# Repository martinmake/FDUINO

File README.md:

# slate_vixen
## DISCLAIMER
This project depends on: https://github.com/martinmake/AVR_libs.git
## HOW TO COMPILE
1. configure LDIR in Makefile
2. make
3. enjoy

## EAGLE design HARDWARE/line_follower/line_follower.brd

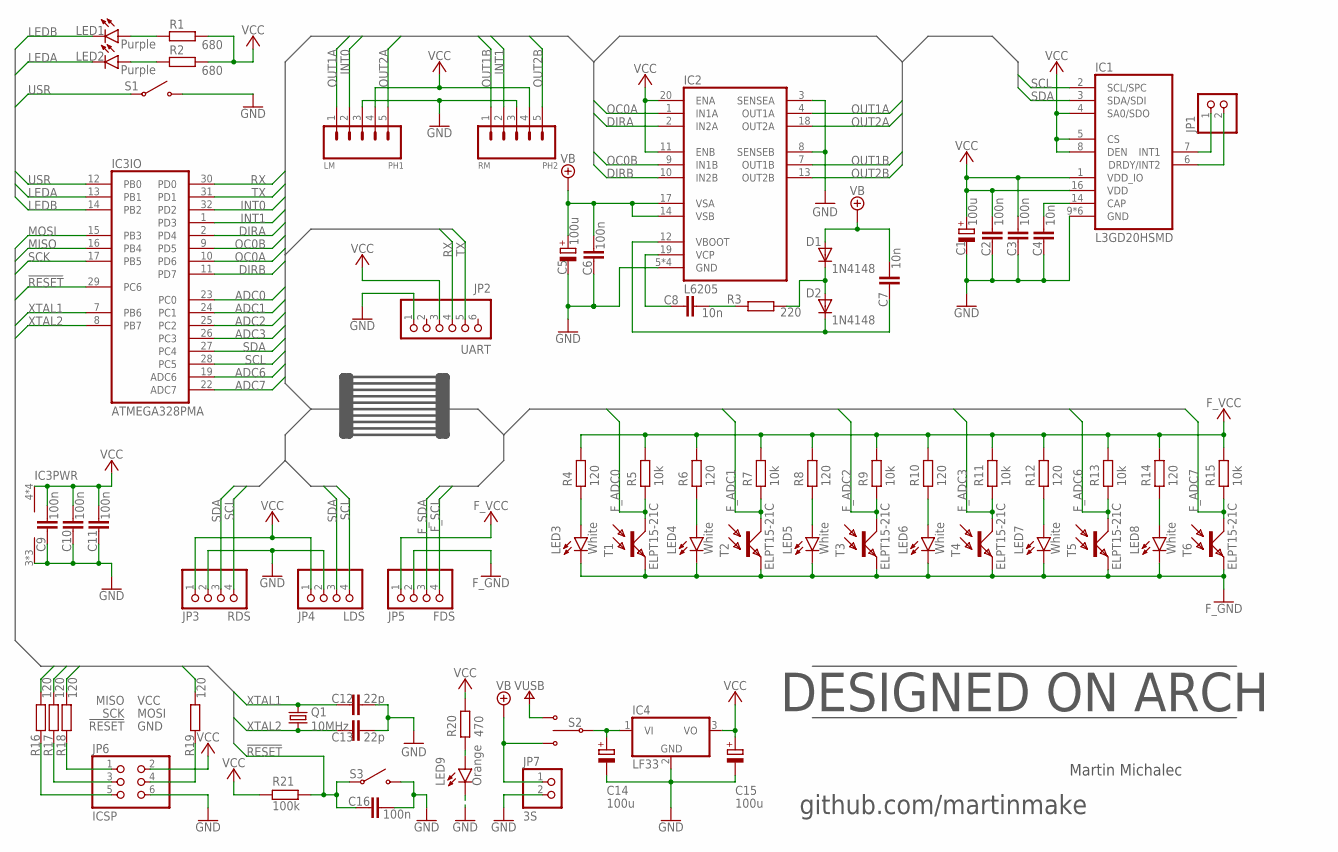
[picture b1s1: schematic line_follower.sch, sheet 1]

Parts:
C1, C5, C14, C15: 100u; UD-6,3X5,8_NICHICON
C2, C3, C6, C9, C10, C11, C16: 100n; C1206
C4, C7, C8: 10n; C1206
C12, C13: 22p; C1206
D1, D2: 1N4148; 1206
IC1: L3GD20HSMD; LGA-16
IC2: L6205; SO20
IC3: ATMEGA328PMA; TQFP32
IC4: LF33; TO220H
JP1: PINHD-1X2; 1X02
JP2: UART; 1X06
JP3: RDS; 1X04/90
JP4: LDS; 1X04/90
JP5: FDS; 1X04/90
JP6: ICSP; 2X03
JP7: 3S; 1X02
LED1, LED2: Purple; SML1206
LED3, LED4, LED5, LED6, LED7, LED8: White; SML1206
LED9: Orange; SML1206
PH1: LM; JST-5-PTH-VERT
PH2: RM; JST-5-PTH-VERT
Q1: 10MHz; CSM-7X-DU
R1, R2: 680; R1206
R3: 220; R1206
R4, R6, R8, R10, R12, R14, R16, R17, R18, R19: 120; R1206
R5, R7, R9, R11, R13, R15: 10k; R1206
R20: 470; R1206
R21: 100k; R1206
S1, S3: BUTTON
S2: DUALSWITCH
T1, T2, T3, T4, T5, T6: ELPT15-21C; 1206

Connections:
!RESET: C16.1, IC3.29 (PC6), R16.2, R21.2, S3.A@1 (1), S3.A@2 (1)
ADC0: IC3.23 (PC0); also elsewhere on the board
ADC1: IC3.24 (PC1); also elsewhere on the board
ADC2: IC3.25 (PC2); also elsewhere on the board
ADC3: IC3.26 (PC3); also elsewhere on the board
ADC6: IC3.19 (ADC6); also elsewhere on the board
ADC7: IC3.22 (ADC7); also elsewhere on the board
DIRA: IC2.2 (IN2A), IC3.2 (PD4)
DIRB: IC2.10 (IN2B), IC3.11 (PD7)
F_ADC0: R5.2, T1.1 (C); also elsewhere on the board
F_ADC1: R7.2, T2.1 (C); also elsewhere on the board
F_ADC2: R9.2, T3.1 (C); also elsewhere on the board
F_ADC3: R11.2, T4.1 (C); also elsewhere on the board
F_ADC6: R13.2, T5.1 (C); also elsewhere on the board
F_ADC7: R15.2, T6.1 (C); also elsewhere on the board
F_GND: JP5.2, LED3.C, LED4.C, LED5.C, LED6.C, LED7.C, LED8.C, T1.2 (E), T2.2 (E), T3.2 (E), T4.2 (E), T5.2 (E), T6.2 (E); also elsewhere on the board
F_SCL: JP5.4; also elsewhere on the board
F_SDA: JP5.3; also elsewhere on the board
F_VCC: JP5.1, R4.1, R5.1, R6.1, R7.1, R8.1, R9.1, R10.1, R11.1, R12.1, R13.1, R14.1, R15.1; also elsewhere on the board
GND: C1.-, C2.2, C3.2, C4.2, C5.-, C6.2, C9.2, C10.2, C11.2, C12.1, C13.1, C14.-, C15.-, C16.2, IC1.9 (GND), IC1.10 (GND), IC1.11 (GND), IC1.12 (GND), IC1.13 (GND), IC1.15 (GND), IC2.3 (SENSEA), IC2.5 (GND), IC2.6 (GND), IC2.8 (SENSEB), IC2.15 (GND), IC2.16 (GND), IC3.3 (GND), IC3.5 (GND), IC3.21 (GND), IC4.2 (GND), JP2.1, JP3.2, JP4.2, JP6.6, JP7.2, LED9.C, PH1.3, PH2.3, S1.B@1 (2), S1.B@2 (2), S3.B@1 (2), S3.B@2 (2); also elsewhere on the board
INT0: IC3.32 (PD2), PH1.2
INT1: IC3.1 (PD3), PH2.2
LEDA: IC3.13 (PB1), LED2.C
LEDB: IC3.14 (PB2), LED1.C
MISO: IC3.16 (PB4), R18.2
MOSI: IC3.15 (PB3), R19.2
unnamed: LED5.A, R8.2
unnamed: C7.1, D2.2 (C), IC2.12 (VBOOT)
unnamed: D1.2 (C), D2.1 (A), R3.2
unnamed: C8.2, R3.1
unnamed: LED1.A, R1.1
unnamed: C4.1, IC1.14 (CAP)
unnamed: C8.1, IC2.19 (VCP)
unnamed: IC1.7 (INT1), JP1.1
unnamed: IC1.6 (DRDY/INT2), JP1.2
unnamed: C14.+, IC4.1 (VI), S2.COM
unnamed: LED6.A, R10.2
unnamed: LED2.A, R2.1
unnamed: LED8.A, R14.2
unnamed: LED7.A, R12.2
unnamed: JP6.1, R18.1
unnamed: LED9.A, R20.2
unnamed: LED4.A, R6.2
unnamed: LED3.A, R4.2
unnamed: JP6.3, R17.1
unnamed: JP6.5, R16.1
unnamed: JP6.4, R19.1
OC0A: IC2.1 (IN1A), IC3.10 (PD6)
OC0B: IC2.9 (IN1B), IC3.9 (PD5)
OUT1A: IC2.4 (OUT1A), PH1.1
OUT1B: IC2.7 (OUT1B), PH2.1
OUT2A: IC2.18 (OUT2A), PH1.5
OUT2B: IC2.13 (OUT2B), PH2.5
RX: IC3.30 (PD0), JP2.4
SCK: IC3.17 (PB5), R17.2
SCL: IC1.2 (SCL/SPC), IC3.28 (PC5), JP3.4, JP4.4; also elsewhere on the board
SDA: IC1.3 (SDA/SDI), IC3.27 (PC4), JP3.3, JP4.3; also elsewhere on the board
TX: IC3.31 (PD1), JP2.5
USR: IC3.12 (PB0), S1.A@1 (1), S1.A@2 (1)
VB: C5.+, C6.1, C7.2, D1.1 (A), IC2.14 (VSB), IC2.17 (VSA), JP7.1, S2.A
VCC: C1.+, C2.1, C3.1, C9.1, C10.1, C11.1, C15.+, IC1.1 (VDD_IO), IC1.4 (SA0/SDO), IC1.5 (CS), IC1.8 (DEN), IC1.16 (VDD), IC2.11 (ENB), IC2.20 (ENA), IC3.4 (VCC), IC3.6 (VCC), IC3.18 (VCC), IC3.20 (VCC), IC4.3 (VO), JP2.3, JP3.1, JP4.1, JP6.2, PH1.4, PH2.4, R1.2, R2.2, R20.1, R21.1; also elsewhere on the board
VUSB: S2.B; also elsewhere on the board
XTAL1: C12.2, IC3.7 (PB6), Q1.2
XTAL2: C13.2, IC3.8 (PB7), Q1.1

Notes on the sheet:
DESIGNED ON ARCH
Martin Michalec
github.com/martinmake

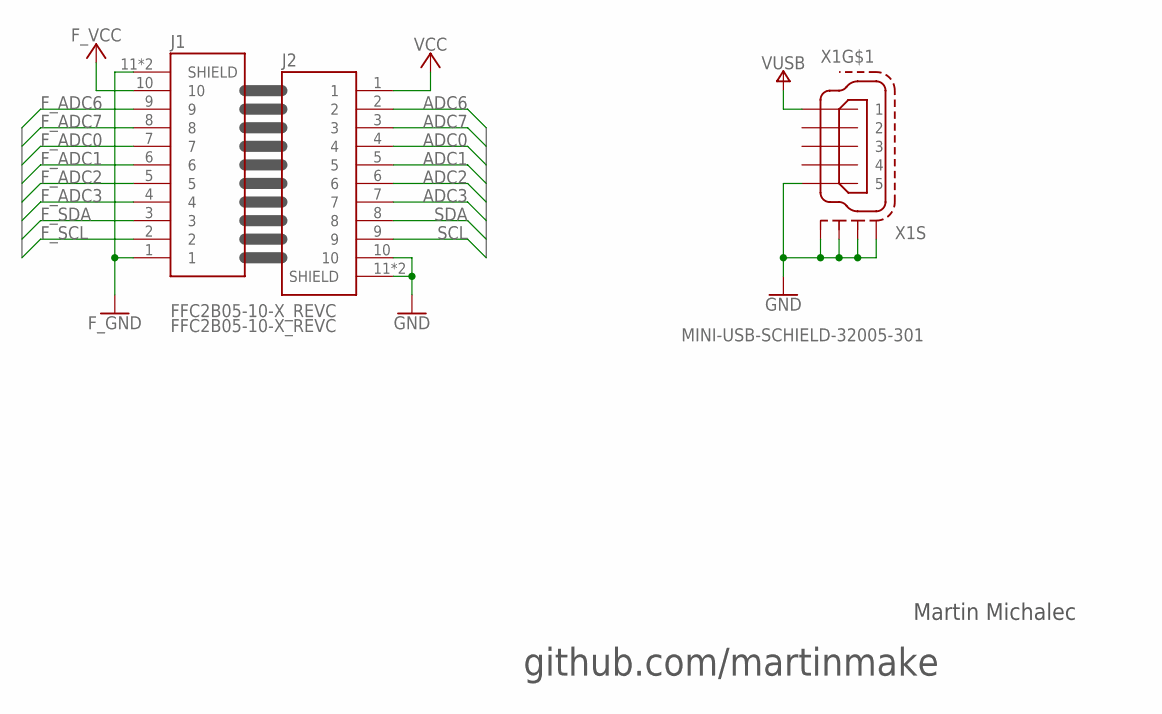
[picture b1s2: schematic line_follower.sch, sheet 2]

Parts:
J1, J2: FFC2B05-10-X_REVC; GCT_FFC2B05-10-X_REVC
X1: MINI-USB-SCHIELD-32005-301; 32005-301

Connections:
ADC0: J2.4; also elsewhere on the board
ADC1: J2.5; also elsewhere on the board
ADC2: J2.6; also elsewhere on the board
ADC3: J2.7; also elsewhere on the board
ADC6: J2.2; also elsewhere on the board
ADC7: J2.3; also elsewhere on the board
F_ADC0: J1.7; also elsewhere on the board
F_ADC1: J1.6; also elsewhere on the board
F_ADC2: J1.5; also elsewhere on the board
F_ADC3: J1.4; also elsewhere on the board
F_ADC6: J1.9; also elsewhere on the board
F_ADC7: J1.8; also elsewhere on the board
F_GND: J1.1, J1.11 (SHIELD), J1.12 (SHIELD); also elsewhere on the board
F_SCL: J1.2; also elsewhere on the board
F_SDA: J1.3; also elsewhere on the board
F_VCC: J1.10; also elsewhere on the board
GND: J2.10, J2.11 (SHIELD), J2.12 (SHIELD), X1.5, X1.M1 (S1), X1.M2 (S2), X1.M3 (S3), X1.M4 (S4); also elsewhere on the board
SCL: J2.9; also elsewhere on the board
SDA: J2.8; also elsewhere on the board
VCC: J2.1; also elsewhere on the board
VUSB: X1.1; also elsewhere on the board

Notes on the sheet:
Martin Michalec
github.com/martinmake

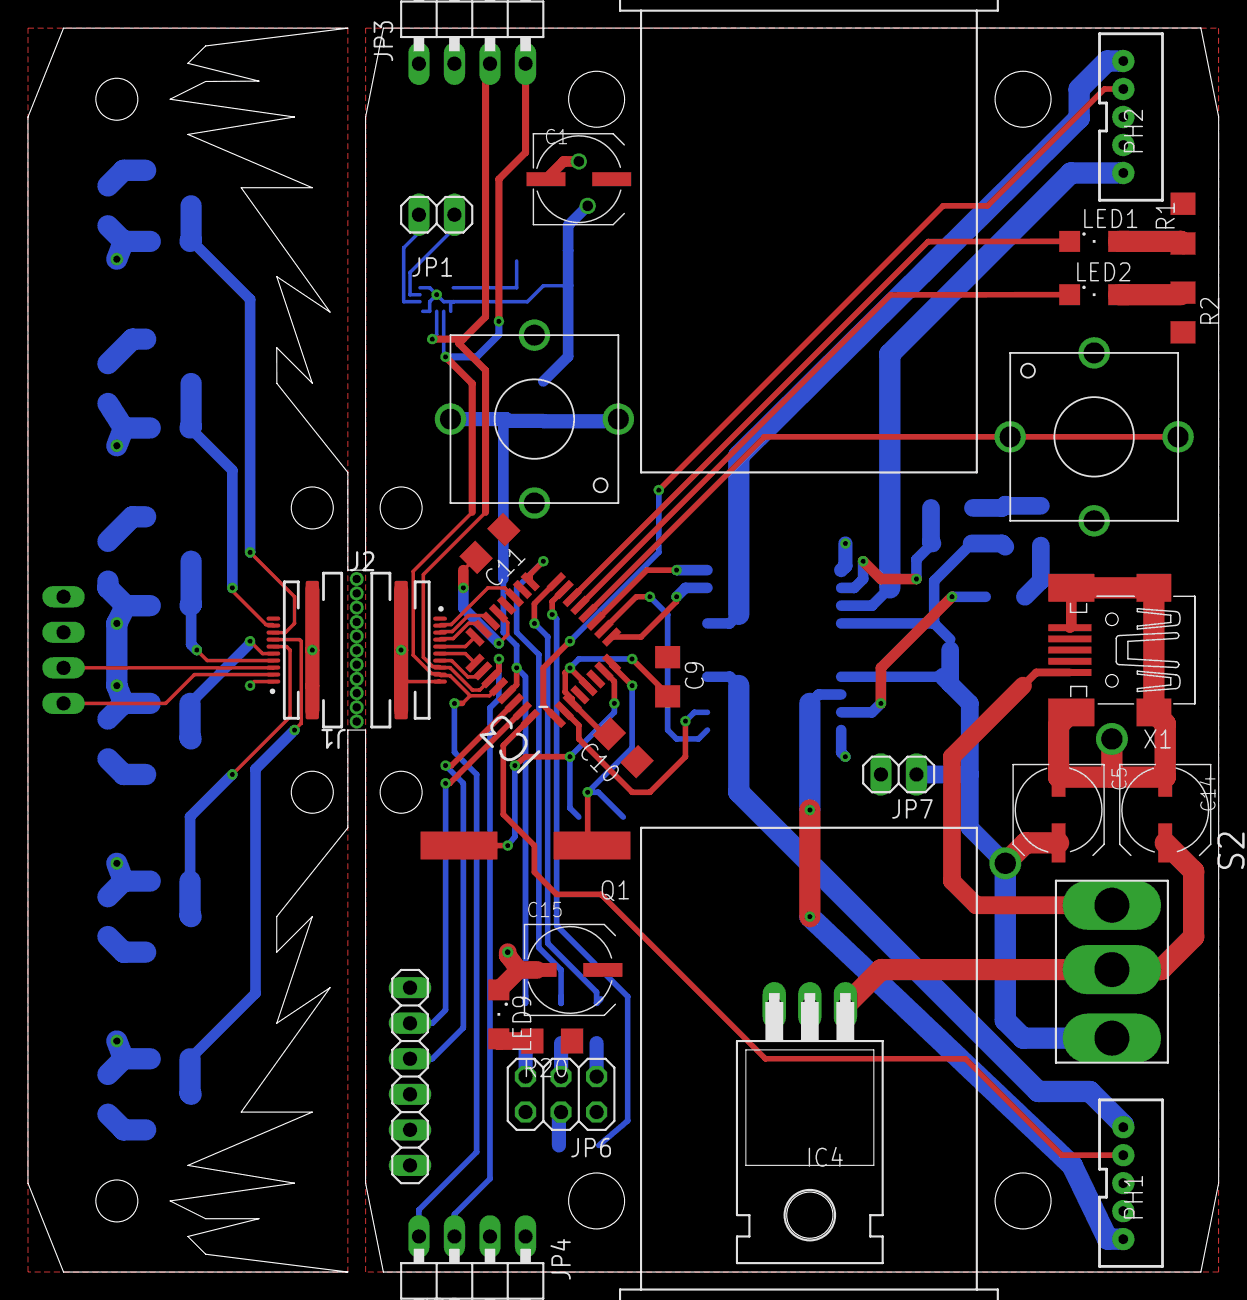
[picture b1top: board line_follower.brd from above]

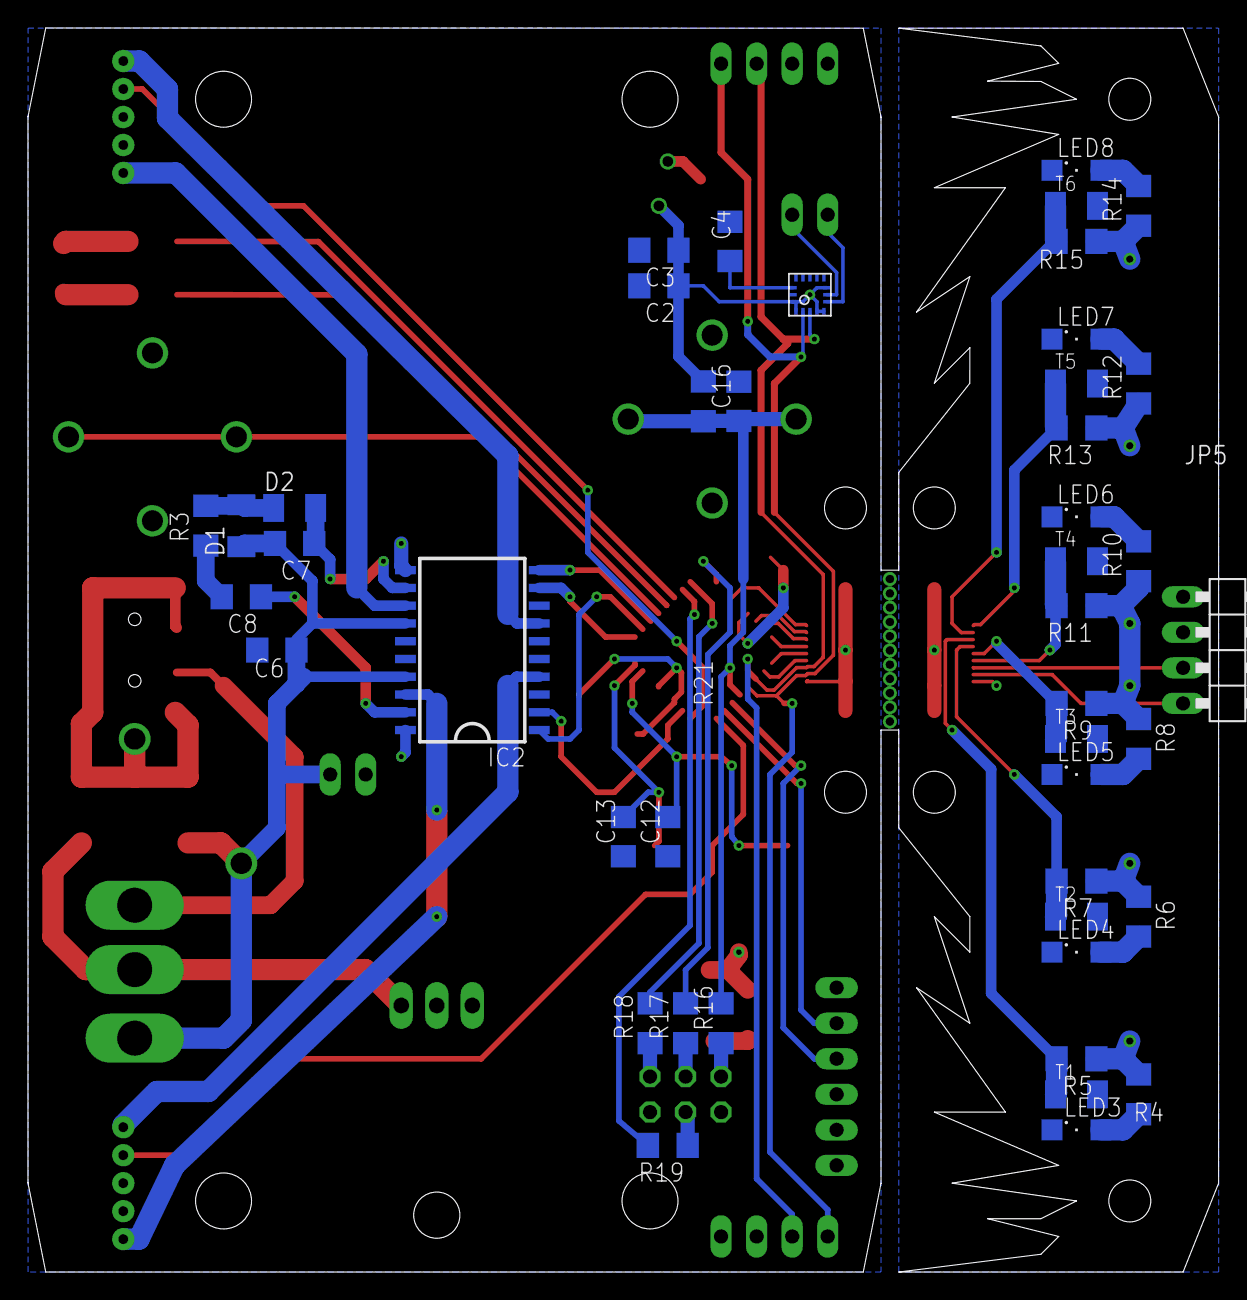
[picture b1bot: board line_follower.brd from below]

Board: 2 copper layers, 85.1 x 88.9 mm, 74 parts (44 on the bottom side), 64 nets.

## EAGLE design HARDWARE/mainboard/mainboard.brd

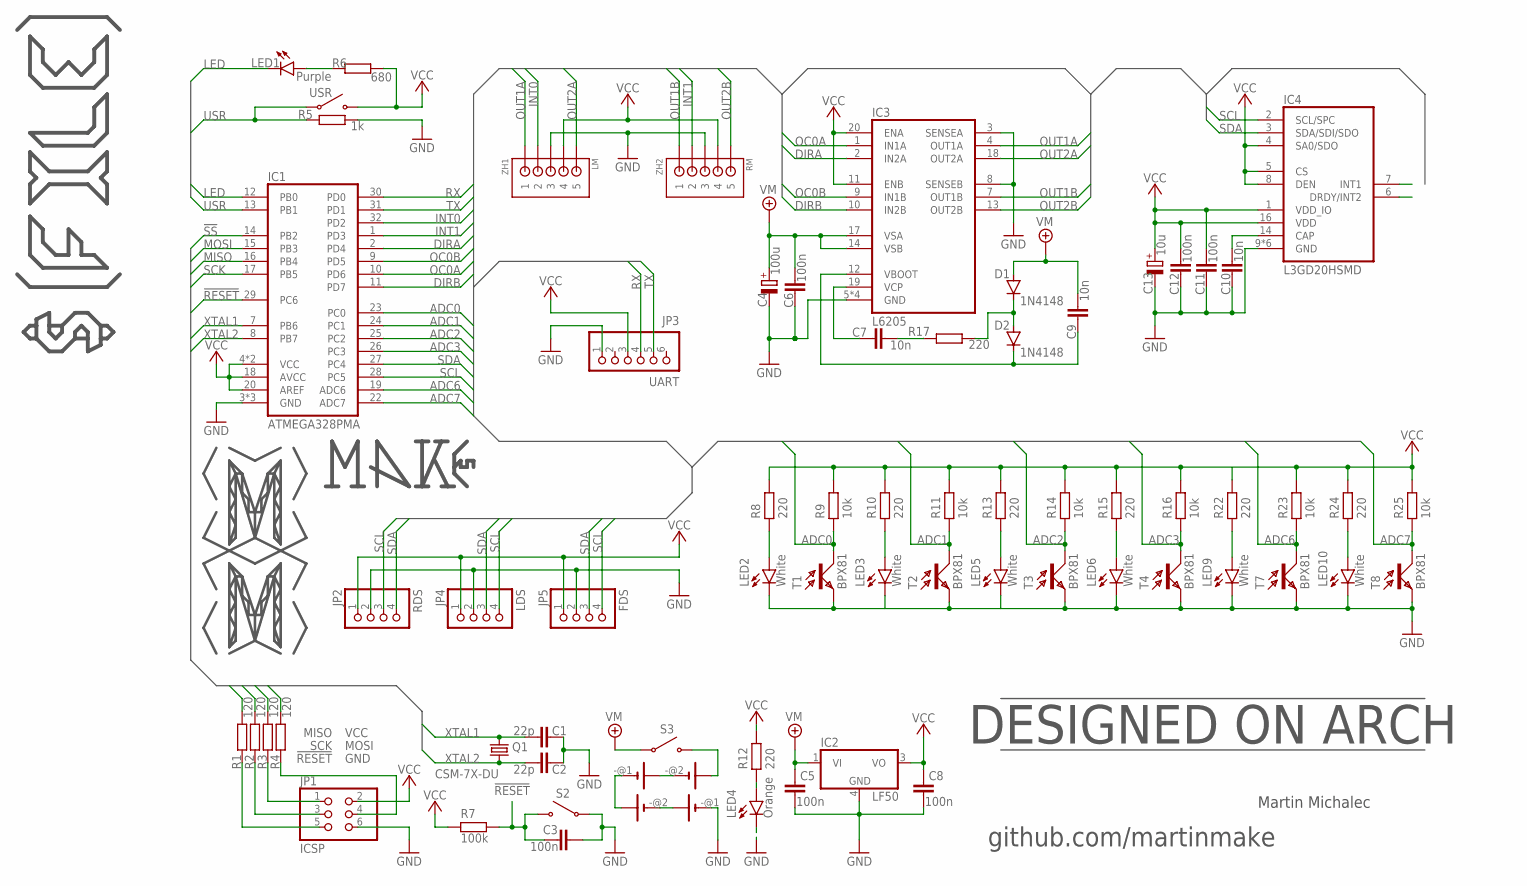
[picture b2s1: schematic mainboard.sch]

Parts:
BAT1, BAT2: BATSERIES; BAT2X18650SERIES
C1, C2: 22p; C1206
C3, C5, C6, C8, C11, C12: 100n; C1206
C4: 100u; SMC_D
C7, C9, C10: 10n; C1206
C13: 10u; SMC_D
D1, D2: 1N4148; DO35-7
IC1: ATMEGA328PMA; TQFP32
IC2: LF50; SOT223
IC3: L6205; SO20
IC4: L3GD20HSMD; LGA-16
JP1: ICSP; 2X03
JP2: RDS; 1X04/90
JP3: UART; 1X06/90
JP4: LDS; 1X04/90
JP5: FDS; 1X04/90
LED1: Purple; SML1206
LED2, LED3, LED5, LED6, LED9, LED10: White; SML1206
LED4: Orange; SML1206
Q1: CSM-7X-DU
R1, R2, R3, R4: 120; R1206
R5: 1k; R1206
R6: 680; R1206
R7: 100k; R1206
R8, R10, R12, R13, R15, R17, R22, R24: 220; R1206
R9, R11, R14, R16, R23, R25: 10k; R1206
S2, S3: SWITCHTHT; SWITCH
T1, T2, T3, T4, T7, T8: BPX81
USR: SWITCHTHT; SWITCH
ZH1: LM; B5B-ZR
ZH2: RM; B5B-ZR

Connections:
!RESET: C3.1, IC1.29 (PC6), R1.2, R7.2, S2.P$2 (2)
!SS: IC1.14 (PB2)
ADC0: IC1.23 (PC0), R9.2, T1.C
ADC1: IC1.24 (PC1), R11.2, T2.C
ADC2: IC1.25 (PC2), R14.2, T3.C
ADC3: IC1.26 (PC3), R16.2, T4.C
ADC6: IC1.19 (ADC6), R23.2, T7.C
ADC7: IC1.22 (ADC7), R25.2, T8.C
DIRA: IC1.2 (PD4), IC3.2 (IN2A)
DIRB: IC1.11 (PD7), IC3.10 (IN2B)
GND: BAT2.-@1 (-), C1.1, C2.1, C3.2, C4.-, C5.2, C6.2, C8.2, C10.2, C11.2, C12.2, C13.-, IC1.3 (GND), IC1.5 (GND), IC1.21 (GND), IC2.4 (GND), IC3.3 (SENSEA), IC3.5 (GND), IC3.6 (GND), IC3.8 (SENSEB), IC3.15 (GND), IC3.16 (GND), IC4.9 (GND), IC4.10 (GND), IC4.11 (GND), IC4.12 (GND), IC4.13 (GND), IC4.15 (GND), JP1.6, JP2.2, JP3.1, JP4.2, JP5.2, LED4.C, R5.2, S2.P$1 (1), ZH1.3, ZH2.3
GND2: LED2.C, LED3.C, LED5.C, LED6.C, LED9.C, LED10.C, T1.E, T2.E, T3.E, T4.E, T7.E, T8.E
INT0: IC1.32 (PD2), ZH1.2
INT1: IC1.1 (PD3), ZH2.2
LED: IC1.12 (PB0), LED1.C
MISO: IC1.16 (PB4), R3.2
MOSI: IC1.15 (PB3), R4.2
unnamed: LED5.A, R13.2
unnamed: C9.1, D2.C, IC3.12 (VBOOT)
unnamed: D1.C, D2.A, R17.2
unnamed: C7.2, R17.1
unnamed: LED1.A, R6.1
unnamed: C10.1, IC4.14 (CAP)
unnamed: C7.1, IC3.19 (VCP)
unnamed: BAT2.+@1 (+), BAT2.-@2 (-)
unnamed: BAT1.+@1 (+), BAT1.-@2 (-)
unnamed: LED6.A, R15.2
unnamed: BAT1.+@2 (+), S3.P$2 (2)
unnamed: BAT1.-@1 (-), BAT2.+@2 (+)
unnamed: LED10.A, R24.2
unnamed: LED9.A, R22.2
unnamed: JP1.1, R3.1
unnamed: LED4.A, R12.2
unnamed: LED3.A, R10.2
unnamed: LED2.A, R8.2
unnamed: JP1.3, R2.1
unnamed: JP1.5, R1.1
unnamed: JP1.4, R4.1
OC0A: IC1.10 (PD6), IC3.1 (IN1A)
OC0B: IC1.9 (PD5), IC3.9 (IN1B)
OUT1A: IC3.4 (OUT1A), ZH1.1
OUT1B: IC3.7 (OUT1B), ZH2.1
OUT2A: IC3.18 (OUT2A), ZH1.5
OUT2B: IC3.13 (OUT2B), ZH2.5
RX: IC1.30 (PD0), JP3.4
SCK: IC1.17 (PB5), R2.2
SCL: IC1.28 (PC5), IC4.2 (SCL/SPC), JP2.3, JP4.4, JP5.4
SDA: IC1.27 (PC4), IC4.3 (SDA/SDI/SDO), JP2.4, JP4.3, JP5.3
TX: IC1.31 (PD1), JP3.5
USR: IC1.13 (PB1), R5.1, USR.P$1 (1)
VCC: C8.1, C11.1, C12.1, C13.+, IC1.4 (VCC), IC1.6 (VCC), IC1.18 (AVCC), IC1.20 (AREF), IC2.3 (VO), IC3.11 (ENB), IC3.20 (ENA), IC4.1 (VDD_IO), IC4.4 (SA0/SDO), IC4.5 (CS), IC4.8 (DEN), IC4.16 (VDD), JP1.2, JP2.1, JP3.3, JP4.1, JP5.1, R6.2, R7.1, R9.1, R11.1, R12.1, R14.1, R16.1, R23.1, R25.1, USR.P$2 (2), ZH1.4, ZH2.4
VM: C4.+, C5.1, C6.1, C9.2, D1.A, IC2.1 (VI), IC3.14 (VSB), IC3.17 (VSA), S3.P$1 (1)
XTAL1: C1.2, IC1.7 (PB6), Q1.2
XTAL2: C2.2, IC1.8 (PB7), Q1.1

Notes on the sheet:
DESIGNED ON ARCH
Martin Michalec
github.com/martinmake

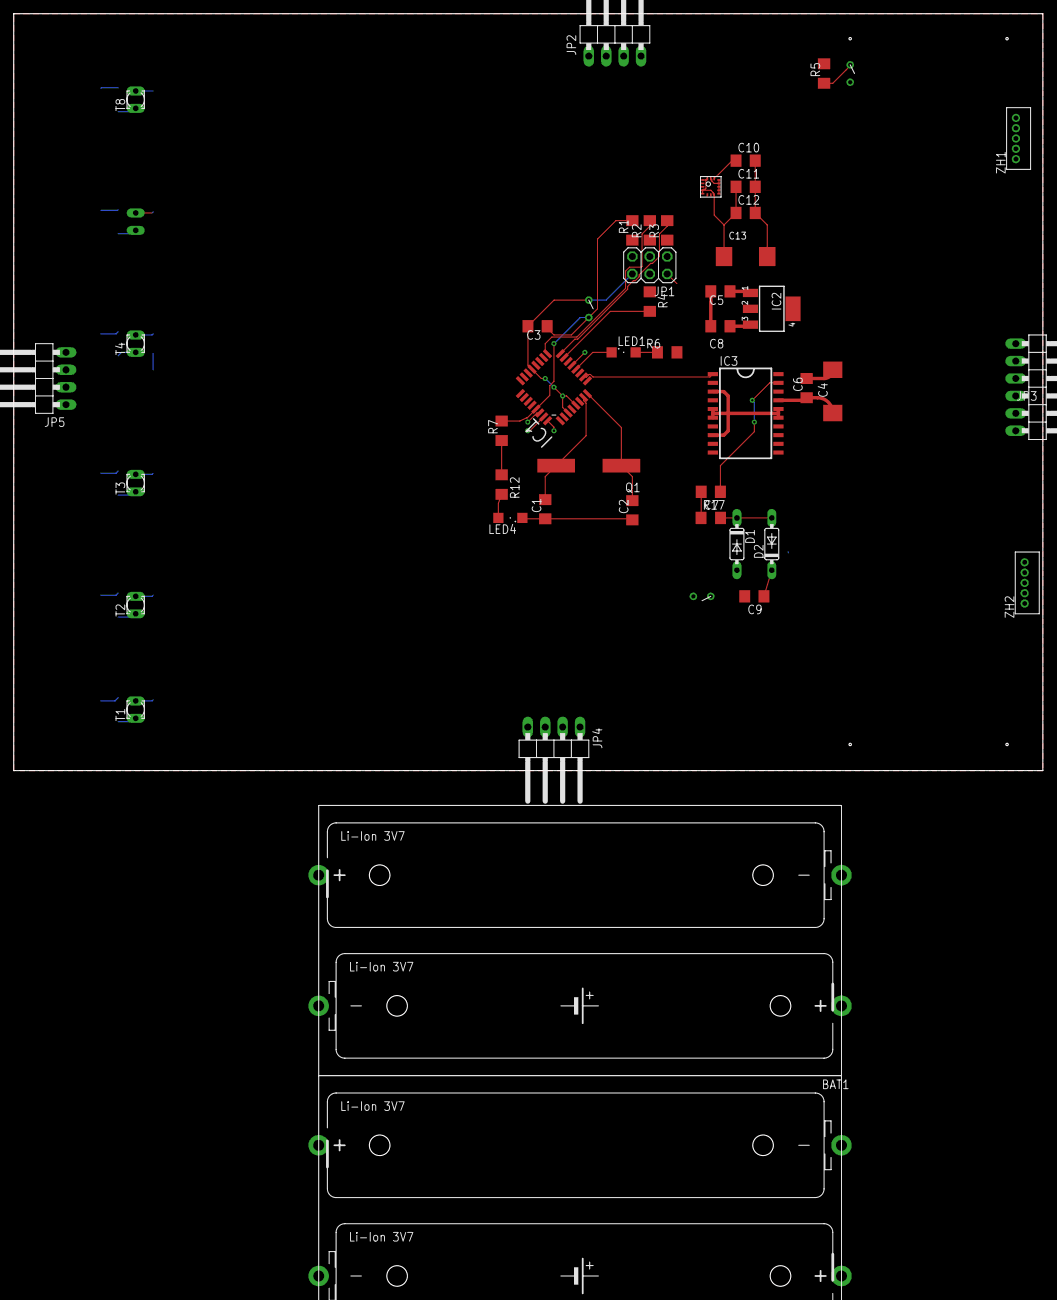
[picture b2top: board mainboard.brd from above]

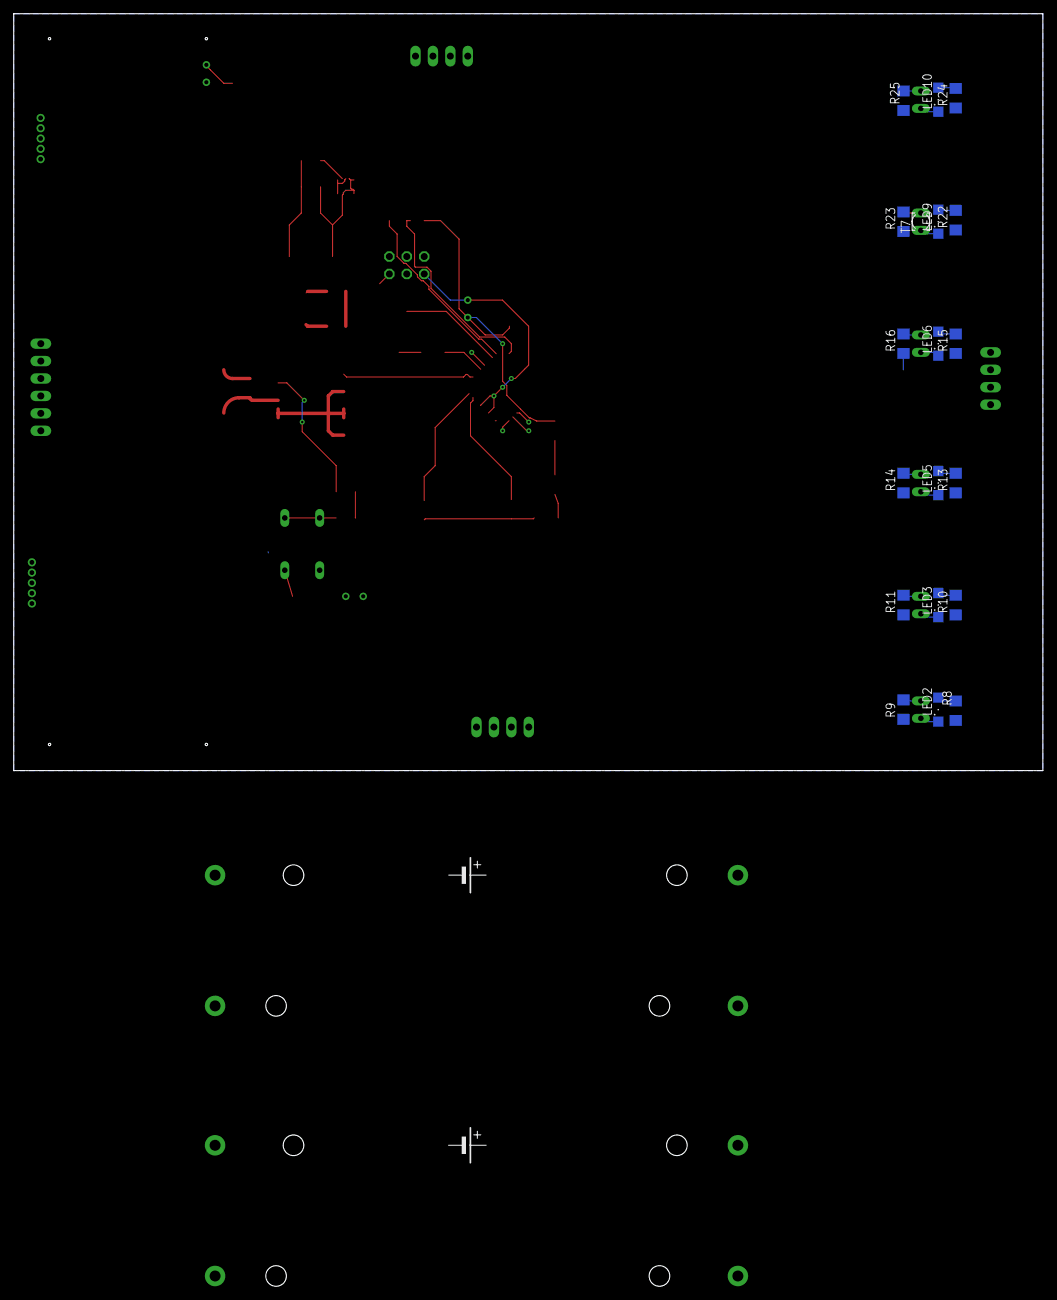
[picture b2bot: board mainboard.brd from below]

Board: 2 copper layers, 150.0 x 110.3 mm, 67 parts (19 on the bottom side), 53 nets.

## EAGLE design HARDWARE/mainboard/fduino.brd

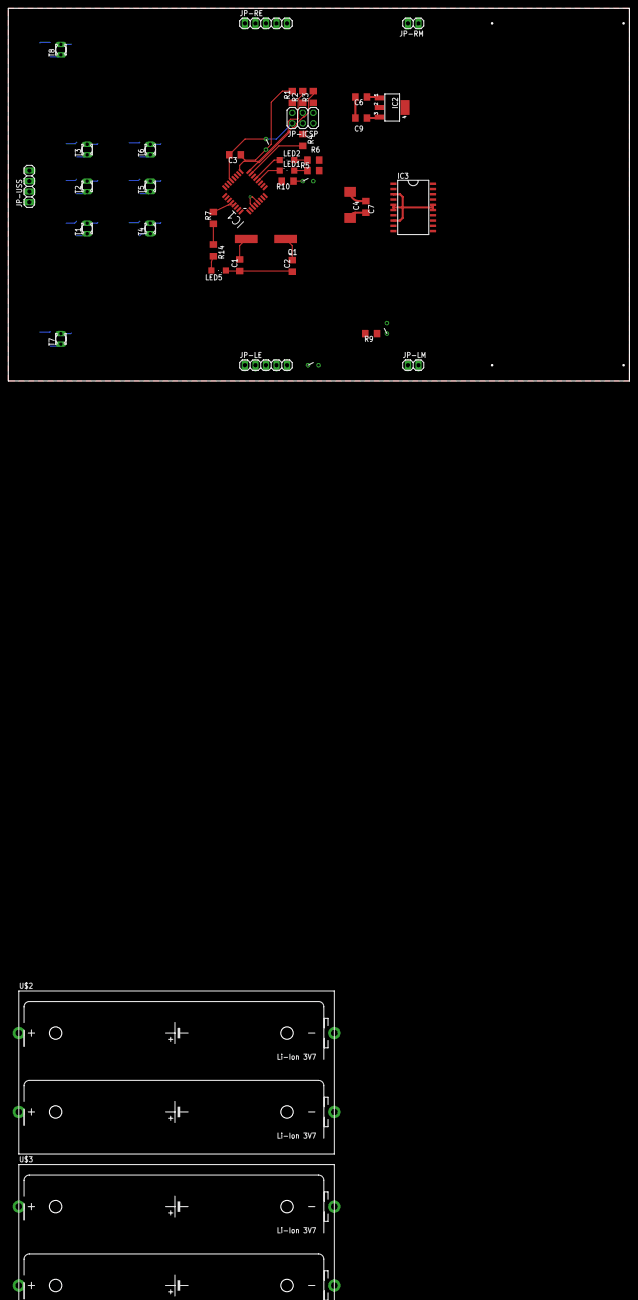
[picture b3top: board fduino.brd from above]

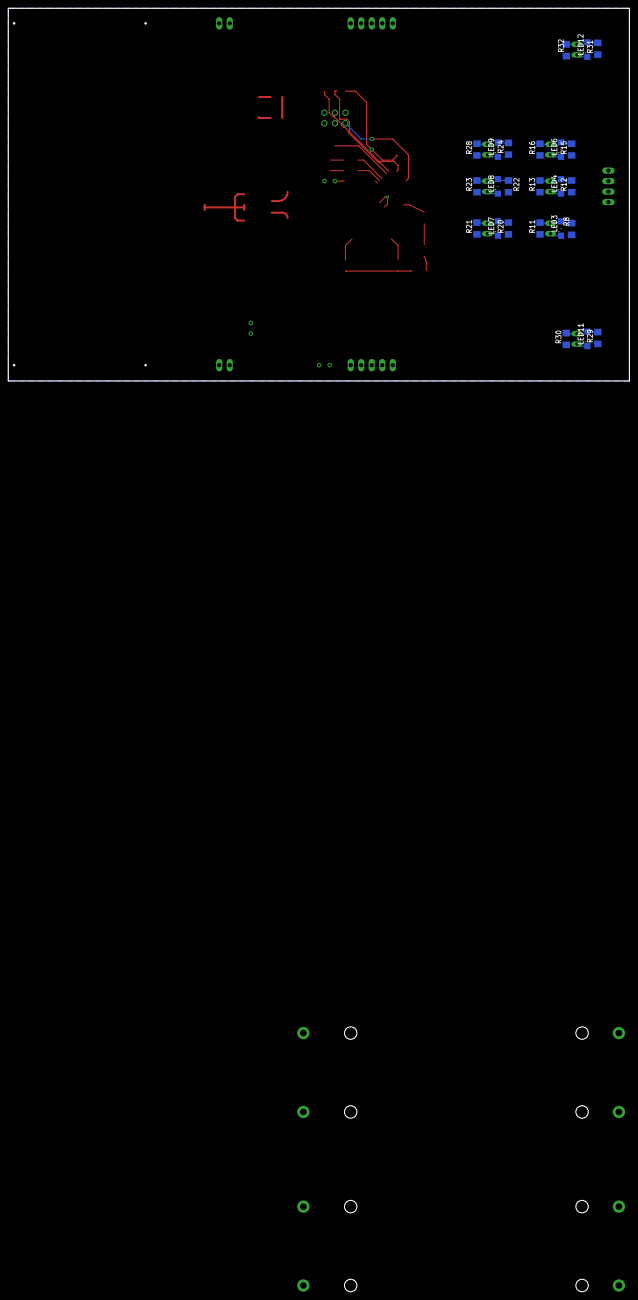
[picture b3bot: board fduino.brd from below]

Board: 2 copper layers, 150.0 x 90.0 mm, 68 parts (24 on the bottom side), 50 nets.

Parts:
C1, C2: 22p; C1206
C3, C6, C7, C9: 100n; C1206
C4: 100u; SMC_D
IC1: ATMEGA328PMA; TQFP32
IC2: LF50; SOT223
IC3: L6205; SO20
JP-ICSP: 2X03
JP-LE: 1X05
JP-LM: 1X02
JP-RE: 1X05
JP-RM: 1X02
JP-USS: 1X04
LED1, LED2: Purple; SML1206
LED3, LED4, LED6, LED7, LED8, LED9, LED11, LED12: White; SML1206
LED5: Orange; SML1206
Q1: CSM-7X-DU
R1, R2, R3, R4: 120; R1206
R5, R6: 680; R1206
R7: 100k; R1206
R8, R12, R14, R15, R20, R22, R24, R29, R31: 220; R1206
R9, R10, R11, R13, R16, R21, R23, R28, R30, R32: 1k; R1206
SW1, SW2, SW3, SW4: SWITCHTHT; SWITCH
T1, T2, T3, T4, T5, T6, T7, T8: BPX81
U$2, U$3: BAT; BAT2X18650

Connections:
!RESET: C3.1, IC1.29, R1.2, R7.2, SW1.P$2
ADC0: IC1.23, R11.2, T1.C
ADC1: IC1.24, R13.2, T2.C
ADC2: IC1.25, R16.2, T3.C
ADC3: IC1.26, R21.2, T4.C
ADC4: IC1.27, R23.2, T5.C
ADC5: IC1.28, R28.2, T6.C
ADC6: IC1.19, R30.2, T7.C
ADC7: IC1.22, R32.2, T8.C
DIRA: IC1.30, IC3.2
DIRB: IC1.31, IC3.10
GND: C1.1, C2.1, C3.2, C4.-, C6.2, C7.2, C9.2, IC1.3, IC1.5, IC1.21, IC2.4, IC3.3, IC3.5, IC3.6, IC3.8, IC3.15, IC3.16, JP-ICSP.6, JP-USS.4, LED5.C, R9.2, R10.2, SW1.P$1, U$3.-@1
GND2: LED3.C, LED4.C, LED6.C, LED7.C, LED8.C, LED9.C, LED11.C, LED12.C, T1.E, T2.E, T3.E, T4.E, T5.E, T6.E, T7.E, T8.E
MISO: IC1.16, R3.2
MOSI: IC1.15, R4.2
unnamed: LED6.A, R15.2
unnamed: IC3.13, JP-RM.2
unnamed: LED2.A, R6.1
unnamed: LED1.A, R5.1
unnamed: IC3.7, JP-RM.1
unnamed: IC3.4, JP-LM.1
unnamed: IC3.18, JP-LM.2
unnamed: U$3.+@1, U$3.-@2
unnamed: U$2.+@1, U$2.-@2
unnamed: LED7.A, R20.2
unnamed: SW4.P$2, U$2.+@2
unnamed: U$2.-@1, U$3.+@2
unnamed: LED12.A, R31.2
unnamed: LED8.A, R22.2
unnamed: LED9.A, R24.2
unnamed: LED11.A, R29.2
unnamed: JP-ICSP.1, R3.1
unnamed: LED5.A, R14.2
unnamed: R11.1, R13.1, R16.1, R21.1, R23.1, R28.1, R30.1, R32.1
unnamed: LED4.A, R12.2
unnamed: LED3.A, R8.2
unnamed: JP-ICSP.3, R2.1
unnamed: JP-ICSP.5, R1.1
unnamed: JP-ICSP.4, R4.1
OC0A: IC1.10, IC3.1
OC0B: IC1.9, IC3.9
PB0: IC1.12, LED1.C
PB1: IC1.13, LED2.C
SCK: IC1.17, R2.2
SW1: IC1.2, R9.1, SW2.P$1
SW2: IC1.11, R10.1, SW3.P$1
VCC: C9.1, IC1.4, IC1.6, IC1.18, IC1.20, IC2.3, IC3.11, IC3.12, IC3.19, IC3.20, JP-ICSP.2, JP-USS.1, R5.2, R6.2, R7.1, R14.1, SW2.P$2, SW3.P$2
VM: C4.+, C6.1, C7.1, IC2.1, IC3.14, IC3.17, SW4.P$1
XTAL1: C1.2, IC1.7, Q1.2
XTAL2: C2.2, IC1.8, Q1.1

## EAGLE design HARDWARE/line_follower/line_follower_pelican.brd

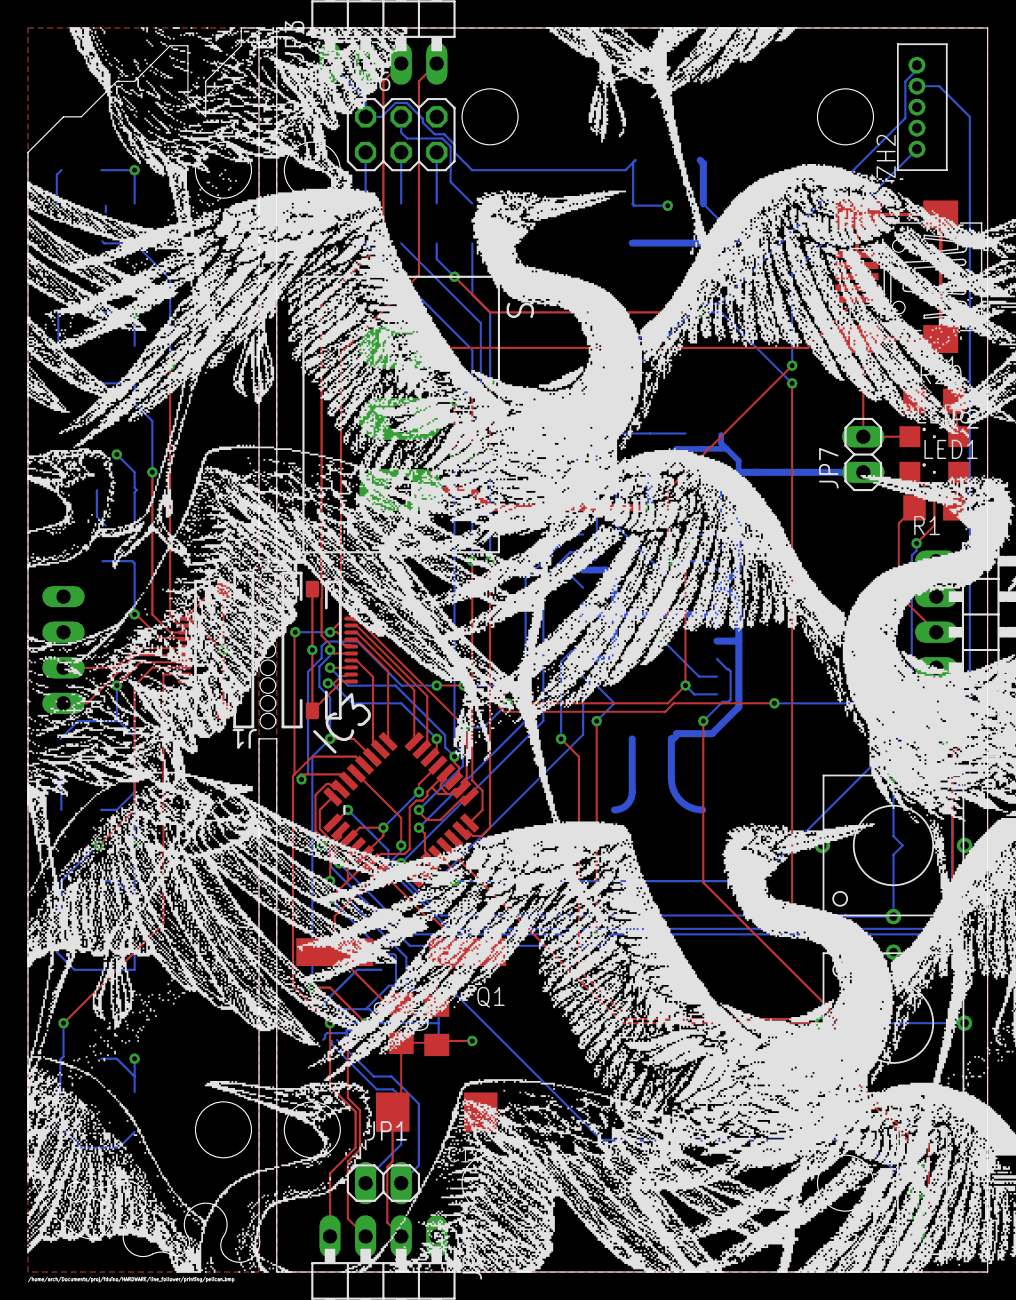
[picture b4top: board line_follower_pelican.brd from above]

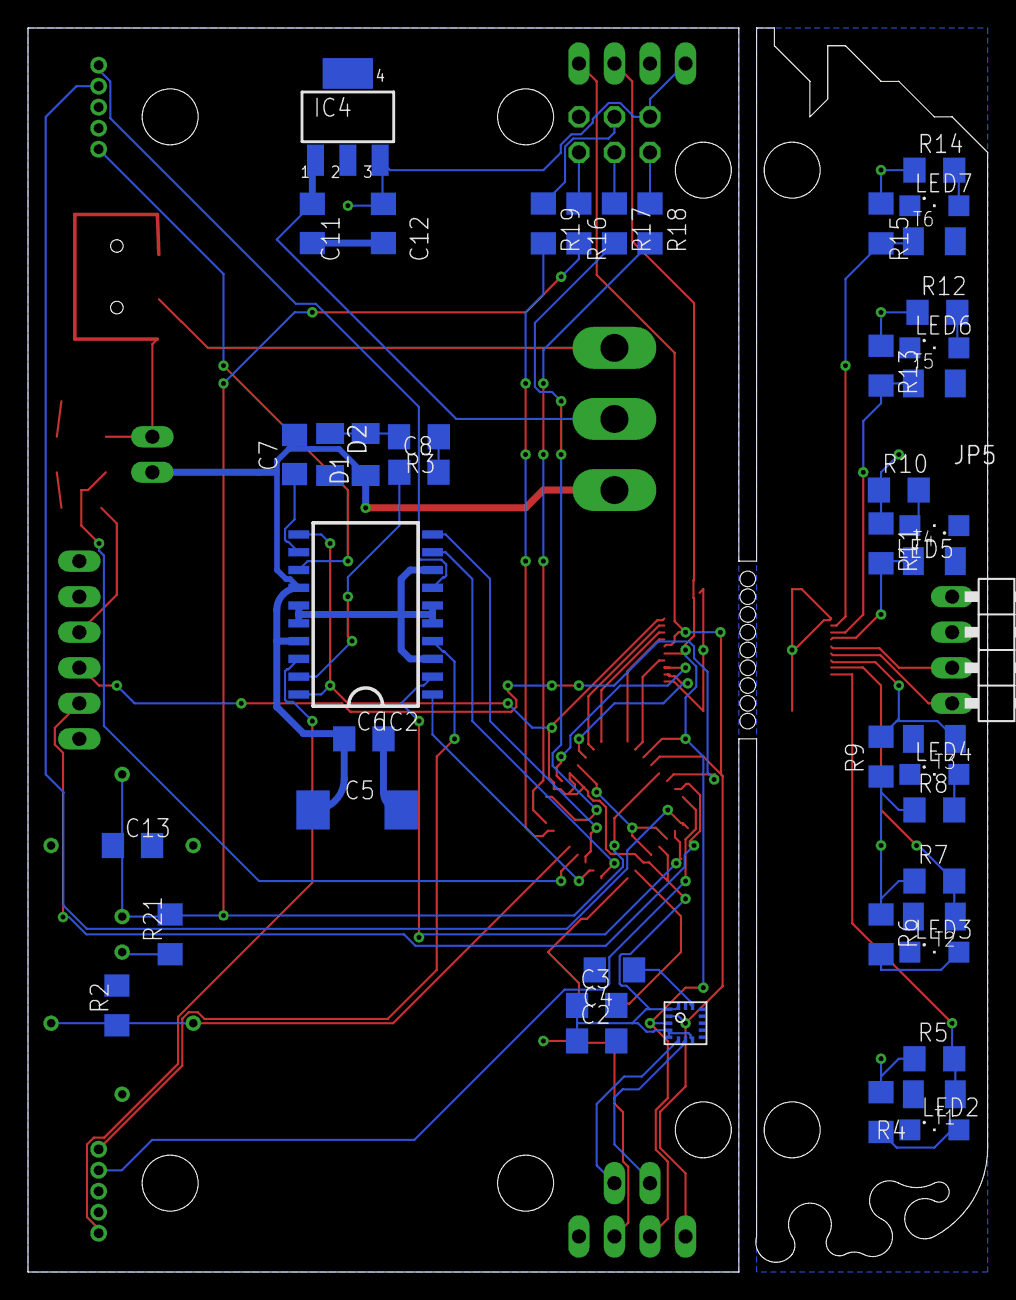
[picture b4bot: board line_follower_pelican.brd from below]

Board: 2 copper layers, 68.6 x 88.9 mm, 70 parts (47 on the bottom side), 62 nets.

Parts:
C1: 10u; SMC_D
C2, C3, C6, C11, C12, C13: 100n; C1206
C4, C7, C8: 10n; C1206
C5: 100u; SMC_D
C9, C10: 22p; C1206
D1, D2: 1N4148; 1206
IC1: L3GD20HSMD; LGA-16
IC2: L6205; SO20
IC3: ATMEGA328PMA; TQFP32
IC4: LF33; SOT223
J1, J2: FFC2B05-10-X_REVC; GCT_FFC2B05-10-X_REVC
JP1: 1X02
JP2: UART; 1X06/90
JP3: RDS; 1X04/90
JP4: LDS; 1X04/90
JP5: FDS; 1X04/90
JP6: ICSP; 2X03
JP7: 3S/4S; 1X02
LED1: Purple; SML1206
LED2, LED3, LED4, LED5, LED6, LED7: White; SML1206
LED8: Orange; SML1206
Q1: 10MHz; CSM-7X-DU
R1: 680; R1206
R2: 1k; R1206
R3, R4, R6, R8, R10, R12, R14, R20: 220; R1206
R5, R7, R9, R11, R13, R15: 10k; R1206
R16, R17, R18, R19: 120; R1206
R21: 100k; R1206
S1, S3: BUTTON
S2: DUALSWITCH
T1, T2, T3, T4, T5, T6: ELPT15-21C; 1206
X1: MINI-USB-SCHIELD-32005-201; 32005-201
ZH1: LM; B5B-ZR
ZH2: RM; B5B-ZR

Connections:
!RESET: C13.1, IC3.29, R16.2, R21.2, S3.A@1, S3.A@2
ADC0: IC3.23, J2.2
ADC1: IC3.24, J2.3
ADC2: IC3.25, J2.4
ADC3: IC3.26, J2.7
ADC6: IC3.19, J2.8
ADC7: IC3.22, J2.9
DIRA: IC2.2, IC3.2
DIRB: IC2.10, IC3.11
F_ADC0: J1.2, R5.2, T1.1
F_ADC1: J1.3, R7.2, T2.1
F_ADC2: J1.4, R9.2, T3.1
F_ADC3: J1.7, R11.2, T4.1
F_ADC6: J1.8, R13.2, T5.1
F_ADC7: J1.9, R15.2, T6.1
F_GND: J1.10, J1.11, J1.12, JP5.2, LED2.C, LED3.C, LED4.C, LED5.C, LED6.C, LED7.C, T1.2, T2.2, T3.2, T4.2, T5.2, T6.2
F_SCL: J1.5, JP5.4
F_SDA: J1.6, JP5.3
F_VCC: J1.1, JP5.1, R4.1, R5.1, R6.1, R7.1, R8.1, R9.1, R10.1, R11.1, R12.1, R13.1, R14.1, R15.1
GND: C1.-, C2.2, C3.2, C4.2, C5.-, C6.2, C9.1, C10.1, C11.2, C12.2, C13.2, IC1.9, IC1.10, IC1.11, IC1.12, IC1.13, IC1.15, IC2.3, IC2.5, IC2.6, IC2.8, IC2.15, IC2.16, IC3.3, IC3.5, IC3.21, IC4.4, J2.10, J2.11, J2.12, JP2.1, JP3.2, JP4.2, JP6.6, JP7.2, LED8.C, R2.2, S3.B@1, S3.B@2, X1.5, X1.M1, X1.M2, X1.M3, X1.M4, ZH1.3, ZH2.3
INT0: IC3.32, ZH1.2
INT1: IC3.1, ZH2.2
LED: IC3.12, LED1.C
MISO: IC3.16, R18.2
MOSI: IC3.15, R19.2
unnamed: LED4.A, R8.2
unnamed: C7.1, D2.2, IC2.12
unnamed: D1.2, D2.1, R3.2
unnamed: C8.2, R3.1
unnamed: LED1.A, R1.1
unnamed: C4.1, IC1.14
unnamed: C8.1, IC2.19
unnamed: IC1.7, JP1.1
unnamed: IC1.6, JP1.2
unnamed: C11.1, IC4.1, S2.COM
unnamed: LED5.A, R10.2
unnamed: LED7.A, R14.2
unnamed: LED6.A, R12.2
unnamed: JP6.1, R18.1
unnamed: LED8.A, R20.2
unnamed: LED3.A, R6.2
unnamed: LED2.A, R4.2
unnamed: JP6.3, R17.1
unnamed: JP6.5, R16.1
unnamed: JP6.4, R19.1
OC0A: IC2.1, IC3.10
OC0B: IC2.9, IC3.9
OUT1A: IC2.4, ZH1.1
OUT1B: IC2.7, ZH2.1
OUT2A: IC2.18, ZH1.5
OUT2B: IC2.13, ZH2.5
RX: IC3.30, JP2.4
SCK: IC3.17, R17.2
SCL: IC1.2, IC3.28, J2.5, JP3.4, JP4.4
SDA: IC1.3, IC3.27, J2.6, JP3.3, JP4.3
TX: IC3.31, JP2.5
USR: IC3.13, R2.1, S1.A@1, S1.A@2
VB: C5.+, C6.1, C7.2, D1.1, IC2.14, IC2.17, JP7.1, S2.A
VCC: C1.+, C2.1, C3.1, C12.1, IC1.1, IC1.4, IC1.5, IC1.8, IC1.16, IC2.11, IC2.20, IC3.4, IC3.6, IC3.18, IC3.20, IC4.3, J2.1, JP2.3, JP3.1, JP4.1, JP6.2, R1.2, R20.1, R21.1, S1.B@1, S1.B@2, ZH1.4, ZH2.4
VUSB: S2.B, X1.1
XTAL1: C9.2, IC3.7, Q1.2
XTAL2: C10.2, IC3.8, Q1.1

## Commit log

2019-03-15 initial
2019-03-15 common
2019-04-25 added UART connector, USR button, motor connectors, charge pump for motor driver
2019-04-26 added gyroscope and distance sensors
2019-04-28 finished front module
2019-04-28 finished PCB
2019-11-05 switching to cmake

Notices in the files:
parts and their libraries:
SparkFun-Connectors: Licensing: Creative Commons ShareAlike 4.0 International - https://creativecommons.org/licenses/by-sa/4.0
